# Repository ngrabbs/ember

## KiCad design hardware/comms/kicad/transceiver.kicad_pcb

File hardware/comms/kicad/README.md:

# Comms KiCad project

[Comms home](../README.md) · [Open work](../TODO.md)

Open `transceiver.kicad_pro`. This is the current working all-UHF, single-antenna
project; the former “RX rebuild pending” description is superseded.

| File | Purpose |
|---|---|
| `transceiver.kicad_pro` | Project configuration |
| `transceiver.kicad_sch` and child sheets | Schematic hierarchy |
| `transceiver.kicad_pcb` | Board layout |
| `transceiver.kicad_dru` | Project design rules |
| `lib/`, `sym-lib-table`, `fp-lib-table` | Project symbols, footprints, and library registration |

These files remain tracked.

Follow the [schematic guide](../design/schematic_guide.md),
[shared design rules](../../conventions/kicad_jlcpcb_design_rules.md), and
[RF layout guidance](../design/rf_layout_guidelines.md). Use KiCad/Konnect for design
changes. Prior CLI/native export discrepancies require native connectivity checks
before synchronizing the board.

Fabrication outputs belong in [releases](../releases/README.md).

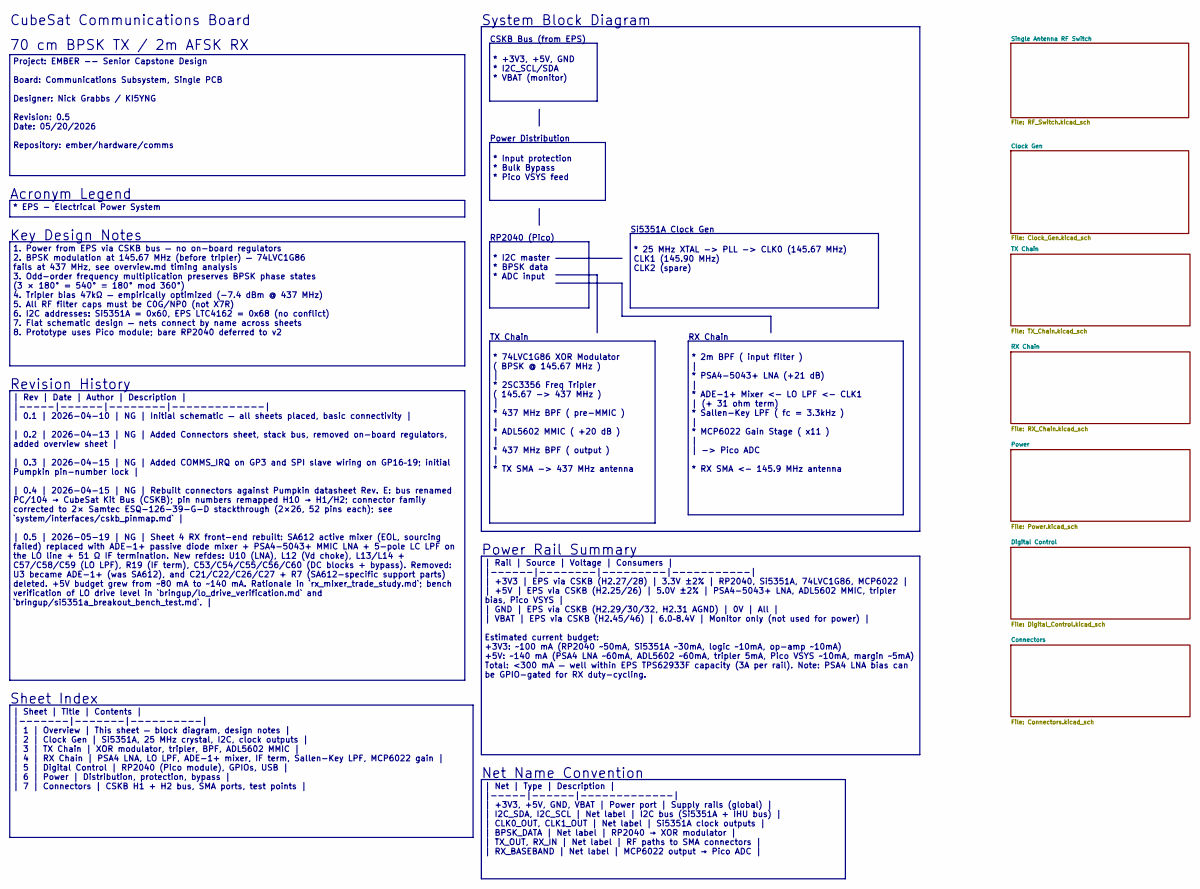
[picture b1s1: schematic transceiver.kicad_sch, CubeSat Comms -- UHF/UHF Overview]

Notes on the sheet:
System Block Diagram
Key Design Notes
Revision History
Si5351A Clock Gen
CSKB Bus (from EPS)
70 cm BPSK TX / 2m AFSK RX
CubeSat Communications Board
Acronym Legend
Power Distribution
Net Name Convention
RX Chain
Power Rail Summary
Sheet Index
RP2040 (Pico)
TX Chain
Project: EMBER -- Senior Capstone Design Board: Communications Subsystem, Single PCB Designer: Nick Grabbs / KI5YNG Revision: 0.5 Date: 05/20/2026 Repository: ember/hardware/comms
| Sheet | Title | Contents | |-------|-------|----------| | 1 | Overview | This sheet — block diagram, design notes | | 2 | Clock Gen | Si5351A, 25 MHz crystal, I2C, clock outputs | | 3 | TX Chain | XOR modulator, tripler, BPF, ADL5602 MMIC | | 4 | RX Chain | PSA4 LNA, LO LPF, ADE-1+ mixer, IF term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
* 74LVC1G86 XOR Modulator ( BPSK @ 145.67 MHz ) | * 2SC3356 Freq Tripler ( 145.67 -> 437 MHz ) | * 437 MHz BPF ( pre-MMIC ) | * ADL5602 MMIC ( +20 dB ) | * 437 MHz BPF ( output ) | * TX SMA -> 437 MHz antenna
* +3V3, +5V, GND * I2C_SCL/SDA * VBAT (monitor)
| Rail | Source | Voltage | Consumers | |------|--------|---------|-----------| | +3V3 | EPS via CSKB (H2.27/28) | 3.3V ±2% | RP2040, Si5351A, 74LVC1G86, MCP6022 | | +5V | EPS via CSKB (H2.25/26) | 5.0V ±2% | PSA4-5043+ LNA, ADL5602 MMIC, tripler bias, Pico VSYS | | GND | EPS via CSKB (H2.29/30/32,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
1. Power from EPS via CSKB bus — no on-board regulators 2. BPSK modulation at 145.67 MHz (before tripler) — 74LVC1G86 fails at 437 MHz, see overview.md timing analysis 3. Odd-order frequency multiplication preserves BPSK phase states (3 × 180° = 540° ≡ 180° mod 360°) 4. Tripler bias 47kΩ — empirica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
* Input protection * Bulk Bypass * Pico VSYS feed
* 25 MHz XTAL -> PLL -> CLK0 (145.67 MHz) CLK1 (145.90 MHz) CLK2 (spare)
| Net | Type | Description | |-----|------|-------------| | +3V3, +5V, GND, VBAT | Power port | Supply rails (global) | | I2C_SDA, I2C_SCL | Net label | I2C bus (Si5351A + IHU bus) | | CLK0_OUT, CLK1_OUT | Net label | Si5351A clock outputs | | BPSK_DATA | Net label | RP2040 → XOR modulator | | TX_O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
* 2m BPF ( input filter ) | * PSA4-5043+ LNA (+21 dB) | * ADE-1+ Mixer <- LO LPF <- CLK1 | (+ 31 ohm term) * Sallen-Key LPF ( fc = 3.3kHz ) | * MCP6022 Gain Stage ( x11 ) | | -> Pico ADC * RX SMA <- 145.9 MHz antenna
| Rev | Date | Author | Description | |-----|------|--------|-------------| | 0.1 | 2026-04-10 | NG | Initial schematic — all sheets placed, basic connectivity | | 0.2 | 2026-04-13 | NG | Added Connectors sheet, stack bus, removed on-board regulators, added overview sheet | | 0.3 | 2026-04-15 | NG 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
* I2C master * BPSK data * ADC input
* EPS - Electrical Power System

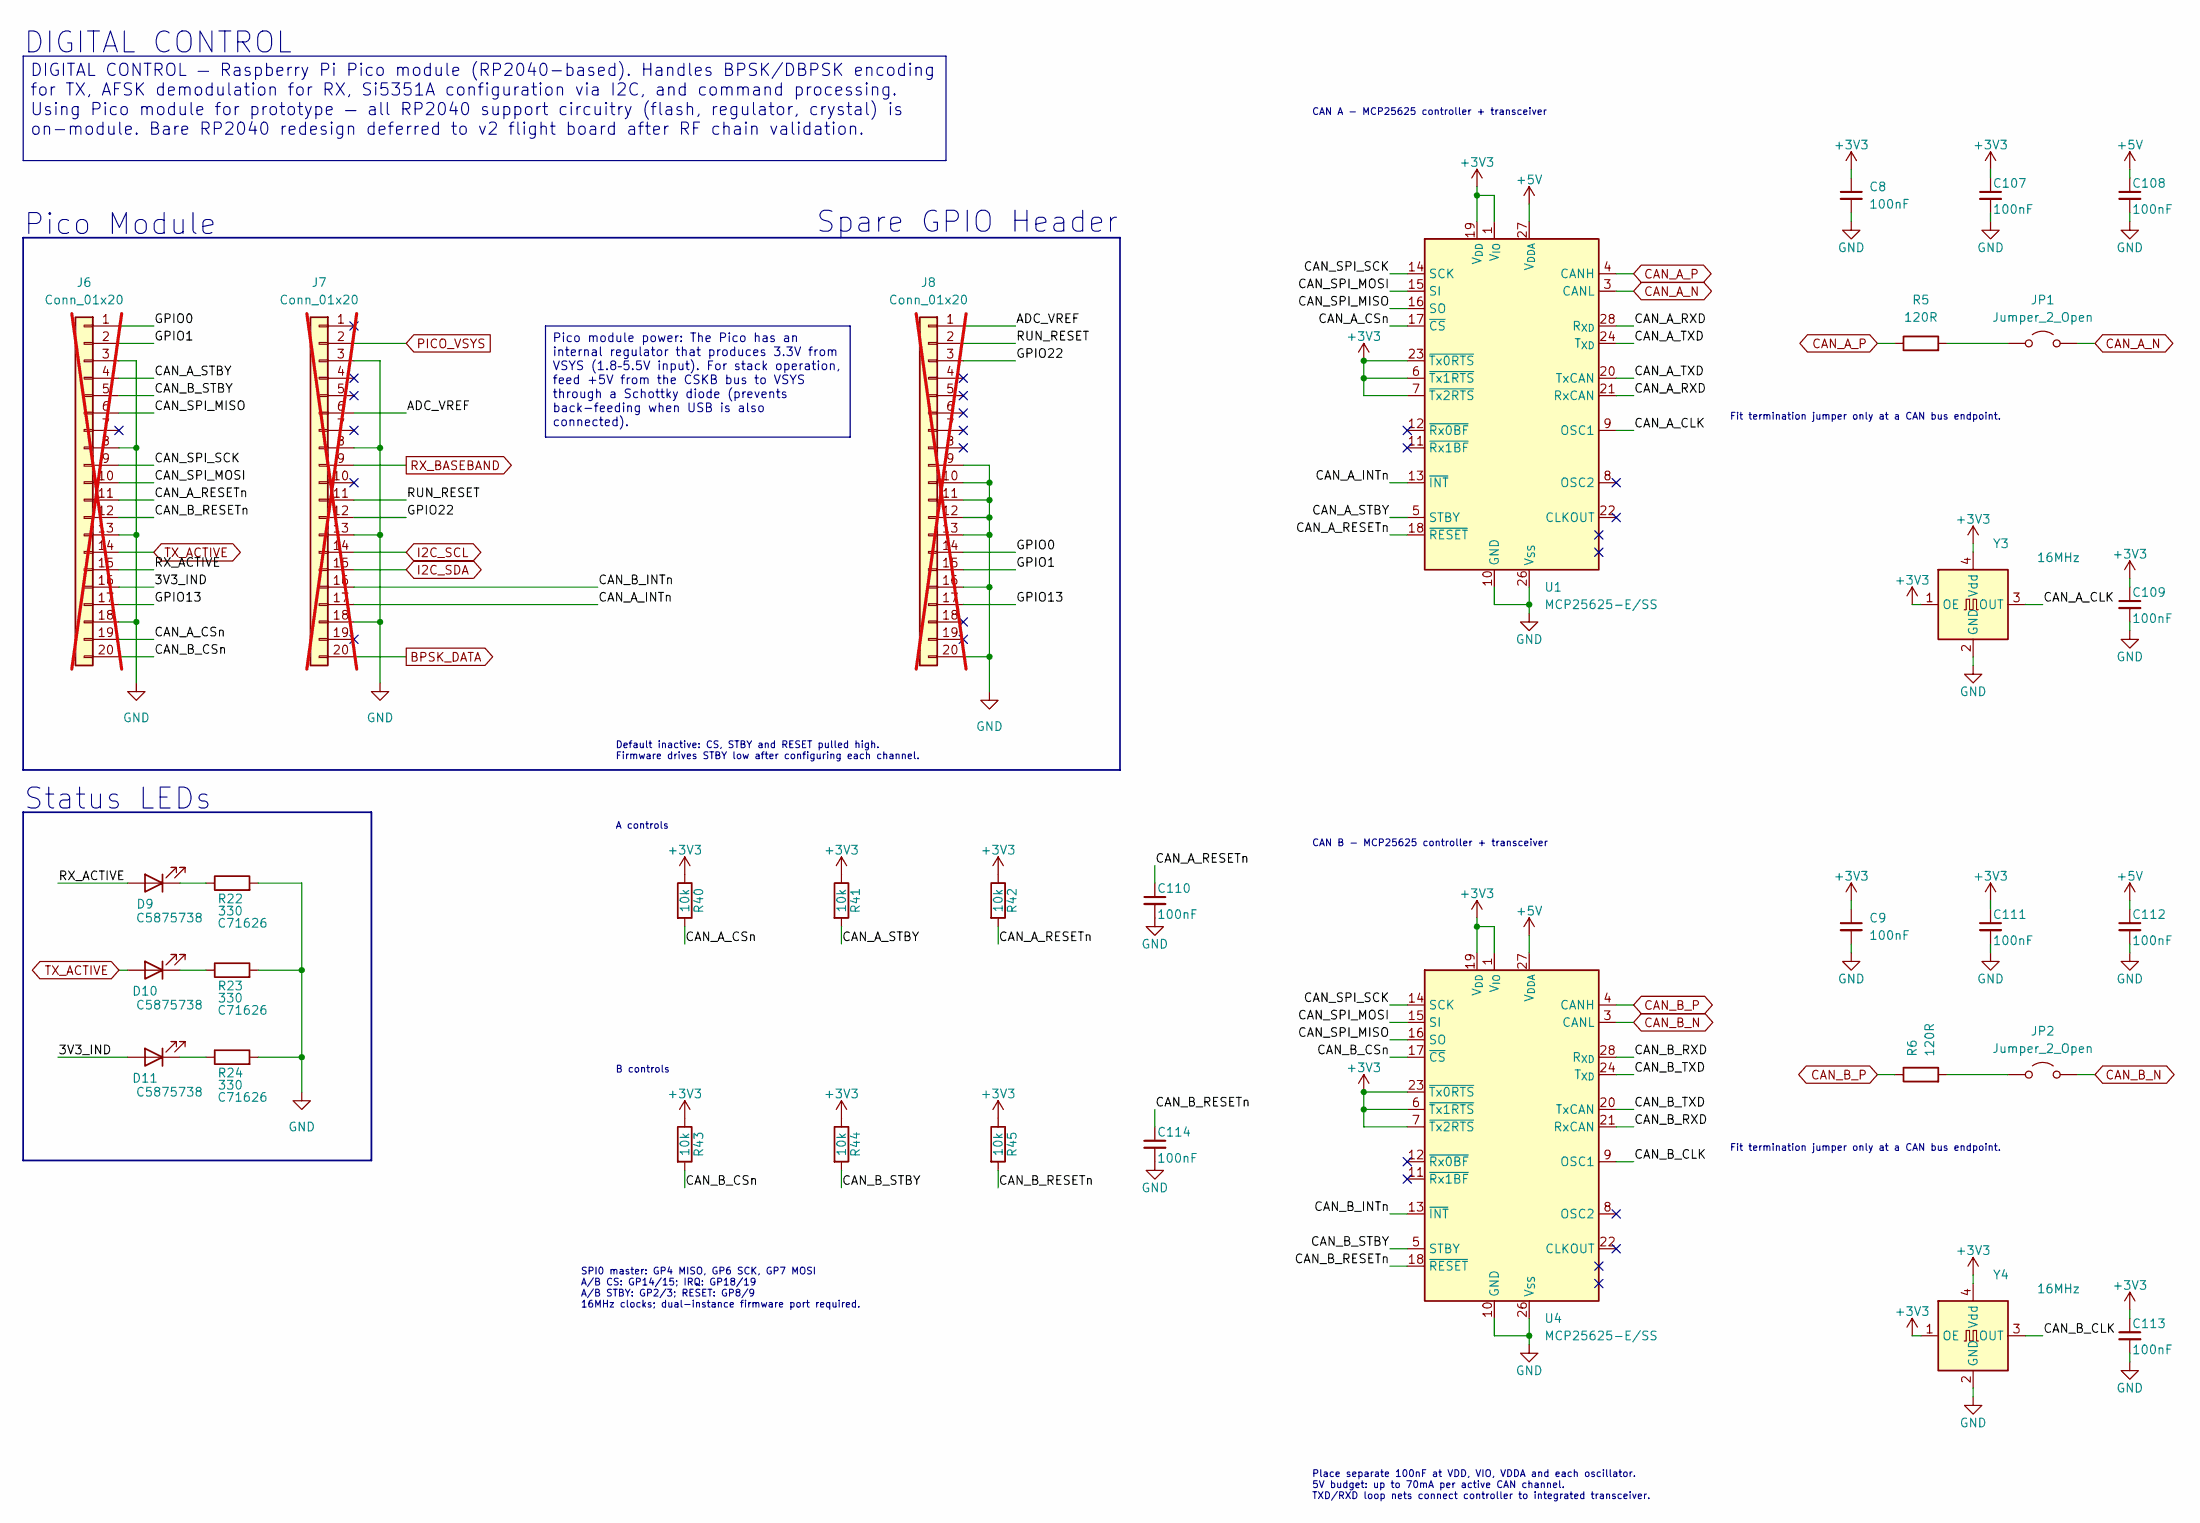
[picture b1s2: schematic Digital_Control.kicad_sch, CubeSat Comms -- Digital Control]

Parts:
C8, C9: 100nF; C_0805_2012Metric; MPN CL21B104KBCNNNC; LCSC Part # C1711
C107, C108, C109, C110, C111, C112, C113, C114: 100nF; C_0603_1608Metric; MPN CC0603KRX7R9BB104; LCSC C14663
D9, D10, D11: LED; LED_0603_1608Metric; LCSC Part # C5875738
J6, J7, J8: Conn_01x20; PinHeader_1x20_P2.54mm_Vertical; MPN 2.54-1*20P; LCSC Part # C50981; not fitted
JP1, JP2: Jumper_2_Open; PinHeader_1x02_P2.54mm_Vertical; MPN 826629-2; LCSC Part # C86471
R5, R6: 120R; R_0805_2012Metric; MPN 0805W8F1200T5E; LCSC Part # C17437
R22, R23, R24: 330; R_0402_1005Metric; LCSC Part # C71626
R40, R41, R42, R43, R44, R45: 10k; R_0603_1608Metric; MPN 0603WAF1002T5E; LCSC C25804
U1, U4: MCP25625-E/SS; SSOP-28_5.3x10.2mm_P0.65mm; MPN MCP25625-E/SS; LCSC C184944
Y3, Y4: 16MHz; Oscillator_SMD_SiT_PQFN-4Pin_7.0x5.0mm; MPN SIT8008AI-82-33E-16.000000Y; LCSC C12710

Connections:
+3V3: C8.1, C9.1, C107.1, C109.1, C111.1, C113.1, R40.1, R41.1, R42.1, R43.1, R44.1, R45.1, U1.1 (V_{IO}), U1.6 (~Tx1RTS), U1.7 (~Tx2RTS), U1.19 (V_{DD}), U1.23 (~Tx0RTS), U4.1 (V_{IO}), U4.6 (~Tx1RTS), U4.7 (~Tx2RTS), U4.19 (V_{DD}), U4.23 (~Tx0RTS), Y3.1 (OE), Y3.4 (Vdd), Y4.1 (OE), Y4.4 (Vdd); also elsewhere on the board
+5V: C108.1, C112.1, U1.27 (V_{DDA}), U4.27 (V_{DDA}); also elsewhere on the board
/Digital Control/3V3_IND: D11.2 (A), J6.16
/Digital Control/ADC_VREF: J7.6, J8.1
/Digital Control/CAN_A_CLK: U1.9 (OSC1), Y3.3 (OUT)
/Digital Control/CAN_A_CSn: J6.19, R40.2, U1.17 (~CS)
/Digital Control/CAN_A_INTn: J7.17, U1.13 (~INT)
/Digital Control/CAN_A_RESETn: C110.1, J6.11, R42.2, U1.18 (~RESET)
/Digital Control/CAN_A_RXD: U1.21 (RxCAN), U1.28 (R_{XD})
/Digital Control/CAN_A_STBY: J6.4, R41.2, U1.5 (STBY)
/Digital Control/CAN_A_TXD: U1.20 (TxCAN), U1.24 (T_{XD})
/Digital Control/CAN_B_CLK: U4.9 (OSC1), Y4.3 (OUT)
/Digital Control/CAN_B_CSn: J6.20, R43.2, U4.17 (~CS)
/Digital Control/CAN_B_INTn: J7.16, U4.13 (~INT)
/Digital Control/CAN_B_RESETn: C114.1, J6.12, R45.2, U4.18 (~RESET)
/Digital Control/CAN_B_RXD: U4.21 (RxCAN), U4.28 (R_{XD})
/Digital Control/CAN_B_STBY: J6.5, R44.2, U4.5 (STBY)
/Digital Control/CAN_B_TXD: U4.20 (TxCAN), U4.24 (T_{XD})
/Digital Control/CAN_SPI_MISO: J6.6, U1.16 (SO), U4.16 (SO)
/Digital Control/CAN_SPI_MOSI: J6.10, U1.15 (SI), U4.15 (SI)
/Digital Control/CAN_SPI_SCK: J6.9, U1.14 (SCK), U4.14 (SCK)
/Digital Control/GPIO0: J6.1, J8.14
/Digital Control/GPIO1: J6.2, J8.15
/Digital Control/GPIO13: J6.17, J8.17
/Digital Control/GPIO22: J7.12, J8.3
/Digital Control/RUN_RESET: J7.11, J8.2
/Digital Control/RX_ACTIVE: D9.2 (A), J6.15
BPSK_DATA: J7.20; also elsewhere on the board
CAN_A_N: JP1.2 (B), U1.3 (CANL); also elsewhere on the board
CAN_A_P: R5.1, U1.4 (CANH); also elsewhere on the board
CAN_B_N: JP2.2 (B), U4.3 (CANL); also elsewhere on the board
CAN_B_P: R6.1, U4.4 (CANH); also elsewhere on the board
GND: C8.2, C9.2, C107.2, C108.2, C109.2, C110.2, C111.2, C112.2, C113.2, C114.2, J6.3, J6.8, J6.13, J6.18, J7.3, J7.8, J7.13, J7.18, J8.9, J8.10, J8.11, J8.12, J8.13, J8.16, J8.20, R22.2, R23.2, R24.2, U1.10 (GND), U1.26 (V_{SS}), U4.10 (GND), U4.26 (V_{SS}), Y3.2 (GND), Y4.2 (GND); also elsewhere on the board
I2C_SCL: J7.14; also elsewhere on the board
I2C_SDA: J7.15; also elsewhere on the board
unnamed: D9.1 (K), R22.1
unnamed: D10.1 (K), R23.1
unnamed: D11.1 (K), R24.1
unnamed: JP1.1 (A), R5.2
unnamed: JP2.1 (A), R6.2
PICO_VSYS: J7.2; also elsewhere on the board
RX_BASEBAND: J7.9; also elsewhere on the board
TX_ACTIVE: D10.2 (A), J6.14; also elsewhere on the board

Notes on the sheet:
Spare GPIO Header
B controls
DIGITAL CONTROL
CAN B - MCP25625 controller + transceiver
CAN A - MCP25625 controller + transceiver
Status LEDs
SPI0 master: GP4 MISO, GP6 SCK, GP7 MOSI A/B CS: GP14/15; IRQ: GP18/19 A/B STBY: GP2/3; RESET: GP8/9 16MHz clocks; dual-instance firmware port required.
Fit termination jumper only at a CAN bus endpoint.
Pico Module
Default inactive: CS, STBY and RESET pulled high. Firmware drives STBY low after configuring each channel.
A controls
Place separate 100nF at VDD, VIO, VDDA and each oscillator. 5V budget: up to 70mA per active CAN channel. TXD/RXD loop nets connect controller to integrated transceiver.
DIGITAL CONTROL — Raspberry Pi Pico module (RP2040-based). Handles BPSK/DBPSK encoding for TX, AFSK demodulation for RX, Si5351A configuration via I2C, and command processing. Using Pico module for prototype — all RP2040 support circuitry (flash, regulator, crystal) is on-module. Bare RP2040 redesi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
Pico module power: The Pico has an internal regulator that produces 3.3V from VSYS (1.8–5.5V input). For stack operation, feed +5V from the CSKB bus to VSYS through a Schottky diode (prevents back-feeding when USB is also connected).

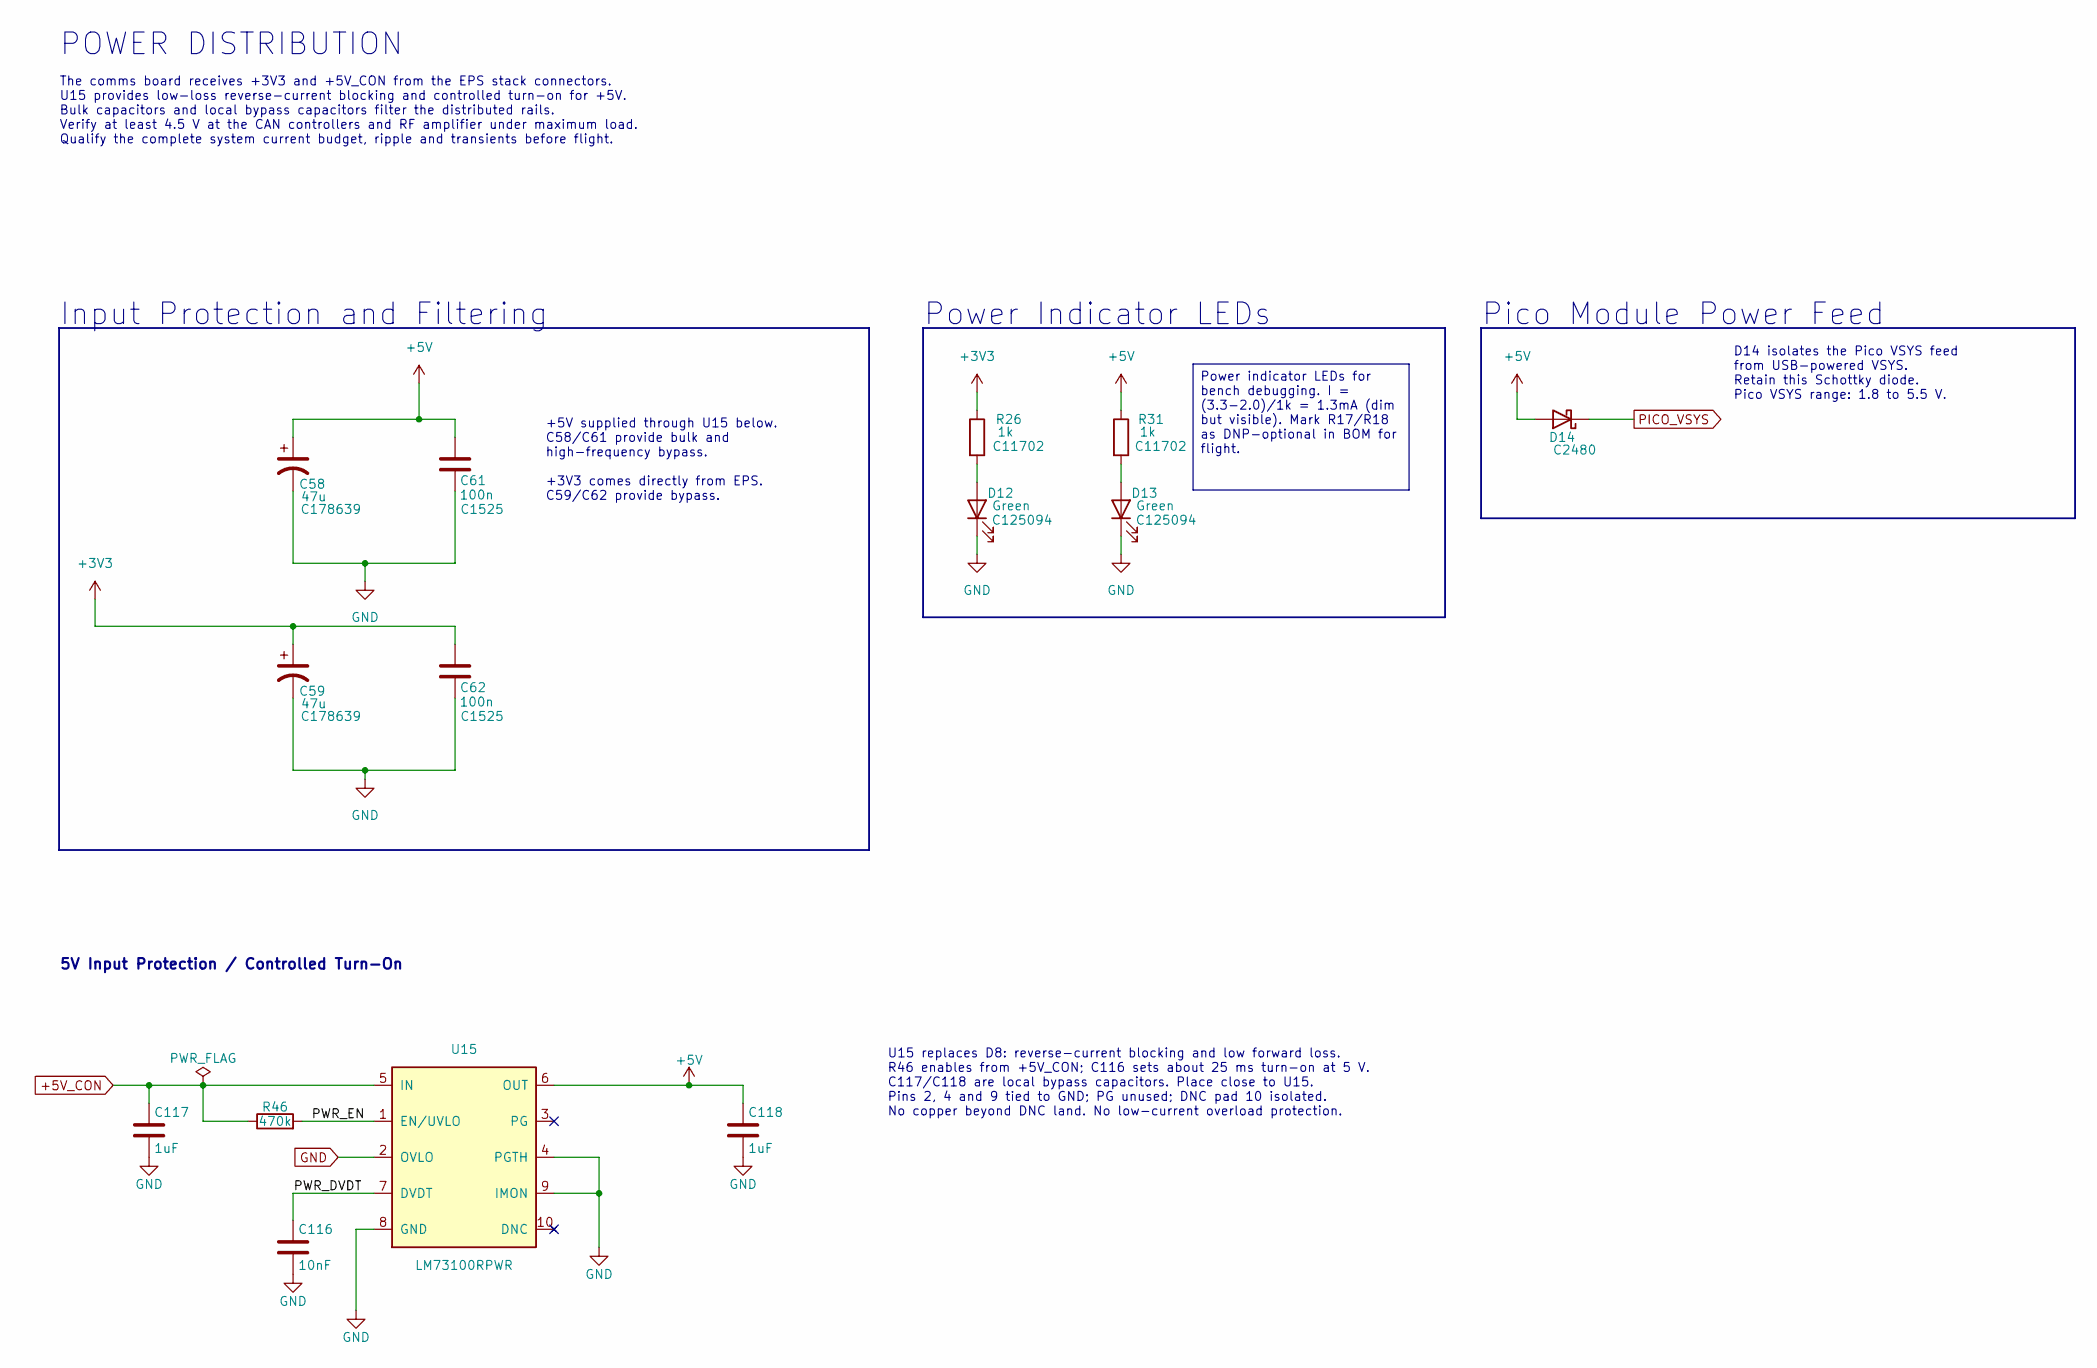
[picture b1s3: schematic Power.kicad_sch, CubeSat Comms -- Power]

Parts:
C58, C59: 47u; CP_Elec_Panasonic_D_6.3x5.8; Voltage 35V; MPN EEHZA1V470P; LCSC Part # C178639
C61, C62: 100n; C_0402_1005Metric; Manufacturer Part # CL05B104KO5NNNC; LCSC Part # C1525
C116: 10nF; C_0603_1608Metric; Tolerance 10%; Voltage Rating 50V; MPN 0603B103K500NT; LCSC Part # C57112
C117, C118: 1uF; C_0603_1608Metric; Tolerance 10%; Voltage Rating 50V; MPN CL10A105KB8NNNC; LCSC Part # C15849
D12, D13: Green; LED_0603_1608Metric; MPN LTST-C190KGKT; LCSC Part # C125094
D14: D_Schottky; D_SMA; LCSC Part # C2480
R26, R31: 1k; R_0402_1005Metric; MPN 0402WGF1001TCE; LCSC Part # C11702
R46: 470k; R_0603_1608Metric; Power Rating 0.1W; Tolerance 1%; MPN 0603WAF4703T5E; LCSC Part # C23178
U15: LM73100RPWR; Texas_RPW0010A_VQFN-HR-10_2x2mm; MPN LM73100RPWR; LCSC Part # C3210761

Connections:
+3V3: C59.1, C62.2, R26.1; also elsewhere on the board
+5V: C58.1, C61.2, C118.1, D14.2 (A), R31.1, U15.6 (OUT); also elsewhere on the board
+5V_CON: C117.1, R46.1, U15.5 (IN); also elsewhere on the board
/Power/PWR_DVDT: C116.1, U15.7 (DVDT)
/Power/PWR_EN: R46.2, U15.1 (EN/UVLO)
GND: C58.2, C59.2, C61.1, C62.1, C116.2, C117.2, C118.2, D12.1 (K), D13.1 (K), U15.2 (OVLO), U15.4 (PGTH), U15.8 (GND), U15.9 (IMON); also elsewhere on the board
unnamed: D12.2 (A), R26.2
unnamed: D13.2 (A), R31.2
PICO_VSYS: D14.1 (K); also elsewhere on the board

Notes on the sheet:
Power Indicator LEDs
+5V supplied through U15 below. C58/C61 provide bulk and high-frequency bypass. +3V3 comes directly from EPS. C59/C62 provide bypass.
5V Input Protection / Controlled Turn-On
Input Protection and Filtering
POWER DISTRIBUTION
Pico Module Power Feed
The comms board receives +3V3 and +5V_CON from the EPS stack connectors. U15 provides low-loss reverse-current blocking and controlled turn-on for +5V. Bulk capacitors and local bypass capacitors filter the distributed rails. Verify at least 4.5 V at the CAN controllers and RF amplifier under maxim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
U15 replaces D8: reverse-current blocking and low forward loss. R46 enables from +5V_CON; C116 sets about 25 ms turn-on at 5 V. C117/C118 are local bypass capacitors. Place close to U15. Pins 2, 4 and 9 tied to GND; PG unused; DNC pad 10 isolated. No copper beyond DNC land. No low-current overload 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
D14 isolates the Pico VSYS feed from USB-powered VSYS. Retain this Schottky diode. Pico VSYS range: 1.8 to 5.5 V.
Power indicator LEDs for bench debugging. I = (3.3-2.0)/1k = 1.3mA (dim but visible). Mark R17/R18 as DNP-optional in BOM for flight.

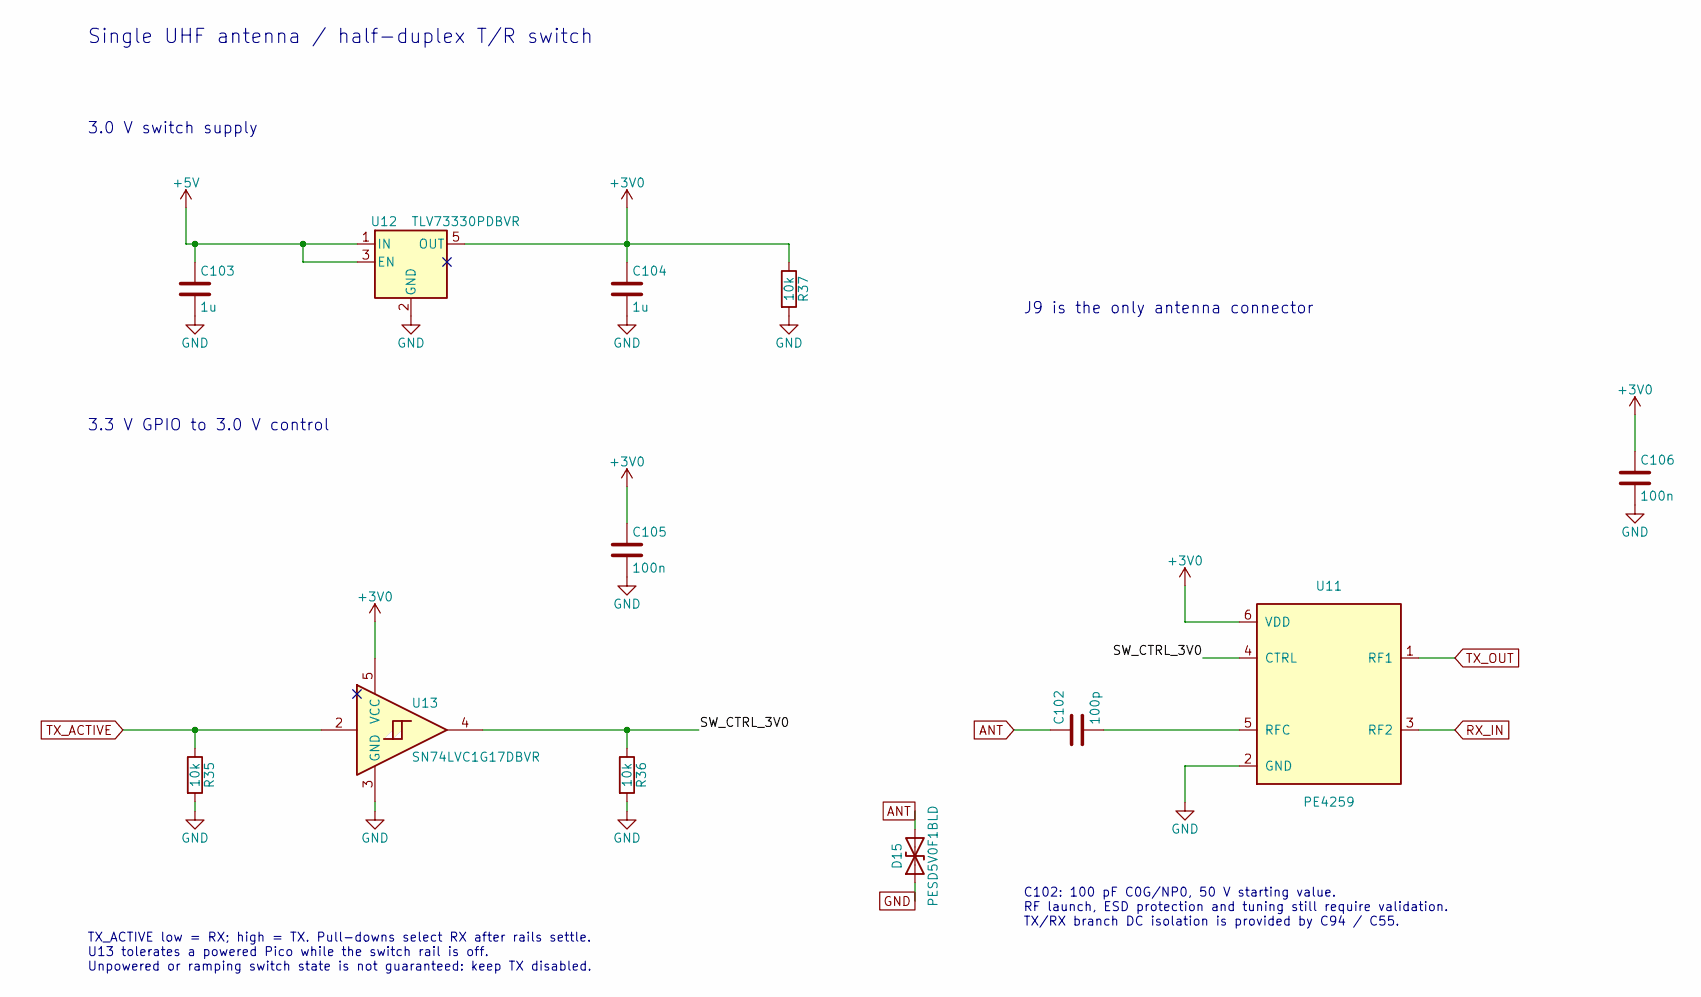
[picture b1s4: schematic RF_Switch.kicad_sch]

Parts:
C102: 100p; C_0402_1005Metric; Tolerance 5%; Voltage 50V; Manufacturer Part # 0402CG101J500NT; LCSC Part # C1546
C103, C104: 1u; C_0603_1608Metric; Voltage 25V; Manufacturer Part # CL10B105KA8NNNC; LCSC Part # C29936
C105, C106: 100n; C_0402_1005Metric; Manufacturer Part # CL05B104KO5NNNC; LCSC Part # C1525
D15: PESD5V0F1BLD; D_SOD-882D; MPN PESD5V0F1BLD,315; LCSC Part # C478204
R35, R36, R37: 10k; R_0402_1005Metric; Manufacturer Part # 0402WGF1002TCE; LCSC Part # C25744
U11: PE4259; SOT-363_SC-70-6; MPN 4259-63; LCSC Part # C470892
U12: TLV73330PDBVR; SOT-23-5; MPN TLV73330PDBVR; LCSC Part # C882826
U13: SN74LVC1G17DBVR; SOT-23-5; MPN SN74LVC1G17DBVR; LCSC Part # C7836

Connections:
+3V0: C104.1, C105.1, C106.1, R37.1, U11.6 (VDD), U12.5 (OUT), U13.5 (VCC)
+5V: C103.1, U12.1 (IN), U12.3 (EN); also elsewhere on the board
/Single Antenna RF Switch/SW_CTRL_3V0: R36.1, U11.4 (CTRL), U13.4
ANT: C102.1, D15.2 (A2); also elsewhere on the board
GND: C103.2, C104.2, C105.2, C106.2, D15.1 (A1), R35.2, R36.2, R37.2, U11.2 (GND), U12.2 (GND), U13.3 (GND); also elsewhere on the board
unnamed: C102.2, U11.5 (RFC)
RX_IN: U11.3 (RF2); also elsewhere on the board
TX_ACTIVE: R35.1, U13.2; also elsewhere on the board
TX_OUT: U11.1 (RF1); also elsewhere on the board

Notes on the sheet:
3.0 V switch supply
C102: 100 pF C0G/NP0, 50 V starting value. RF launch, ESD protection and tuning still require validation. TX/RX branch DC isolation is provided by C94 / C55.
Single UHF antenna / half-duplex T/R switch
3.3 V GPIO to 3.0 V control
J9 is the only antenna connector
TX_ACTIVE low = RX; high = TX. Pull-downs select RX after rails settle. U13 tolerates a powered Pico while the switch rail is off. Unpowered or ramping switch state is not guaranteed: keep TX disabled.

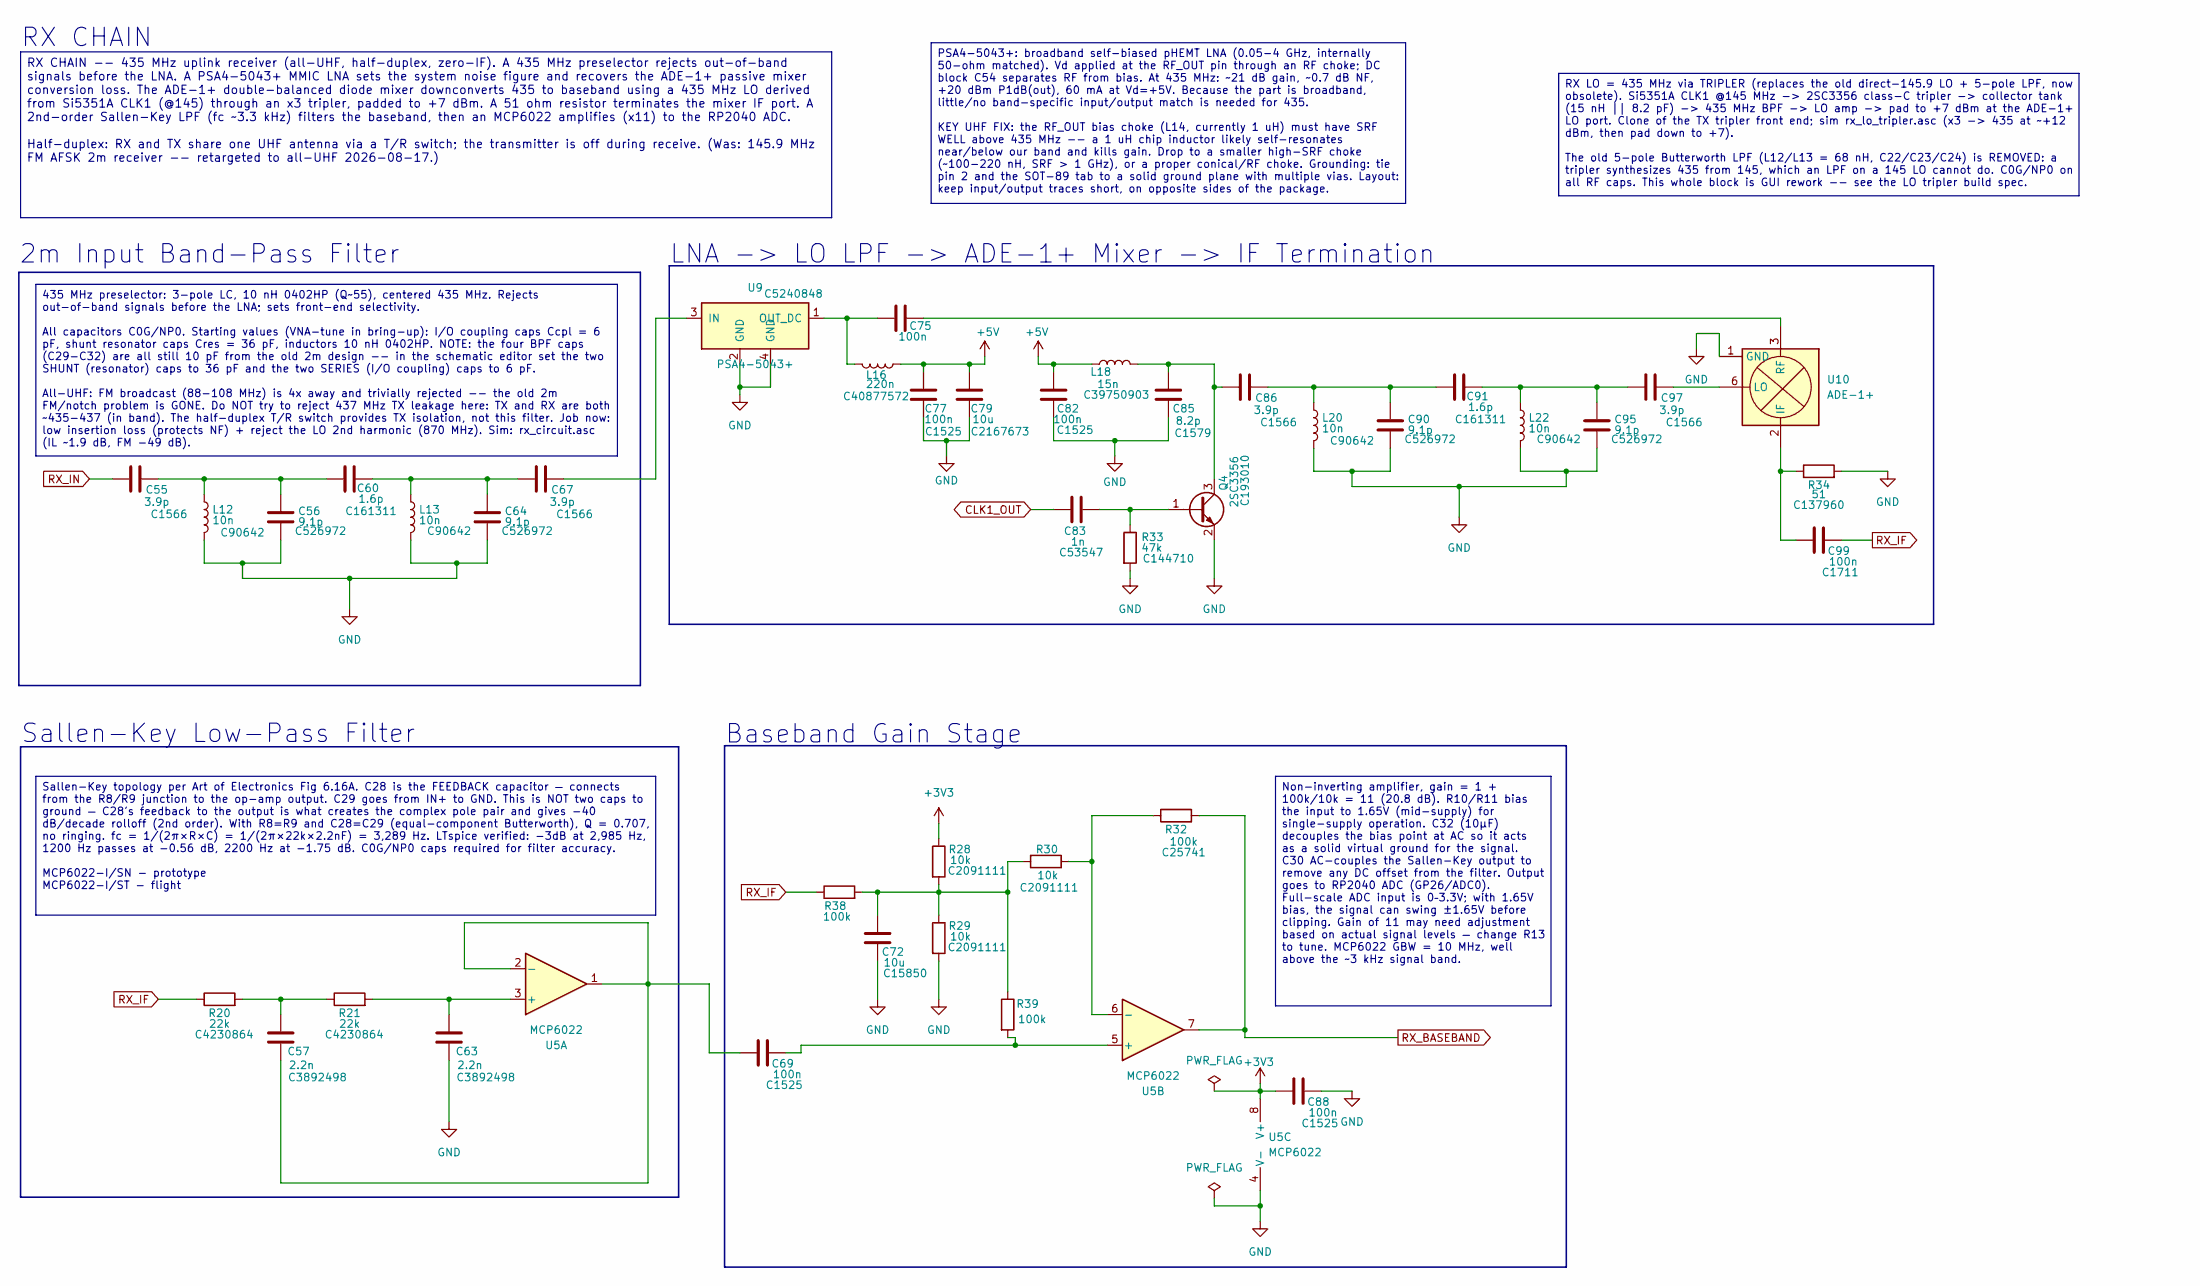
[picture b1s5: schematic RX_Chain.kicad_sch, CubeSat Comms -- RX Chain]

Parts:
C55, C67, C86, C97: 3.9p; C_0402_1005Metric; LCSC Part # C1566
C56, C64, C90, C95: 9.1p; C_0402_1005Metric; LCSC Part # C526972
C57, C63: 2.2n; C_0402_1005Metric; LCSC Part # C3892498
C60, C91: 1.6p; C_0402_1005Metric; LCSC Part # C161311
C69, C75, C77, C82, C88: 100n; C_0402_1005Metric; Manufacturer Part # CL05B104KO5NNNC; LCSC Part # C1525
C72: 10u; C_0805_2012Metric; LCSC Part # C15850
C79: 10u; C_0805_2012Metric; LCSC Part # C2167673
C83: 1n; C_0402_1005Metric; Manufacturer Part # 0402CG102J500NT; LCSC Part # C53547
C85: 8.2p; C_0402_1005Metric; LCSC Part # C1579
C99: 100n; C_0805_2012Metric; Manufacturer Part # CL21B104KBCNNNC; LCSC Part # C1711
L12, L13, L20, L22: 10n; L_0402_1005Metric; MPN LQW15AN10NG00D; LCSC Part # C90642
L16: 220n; L_Coilcraft_0805HP; MPN 0805HP-221XGRC; LCSC Part # C40877572
L18: 15n; L_0402_1005Metric; LCSC Part # C39750903
Q4: 2SC3356; SOT-23; Manufacturer Part # 2SC3356; LCSC Part # C193010
R20, R21: 22k; R_0402_1005Metric; LCSC Part # C4230864
R28, R29, R30: 10k; R_0402_1005Metric; LCSC Part # C2091111
R32, R38, R39: 100k; R_0402_1005Metric; LCSC Part # C25741
R33: 47k; R_0402_1005Metric; LCSC Part # C144710
R34: 51; R_0402_1005Metric; LCSC Part # C137960
U5: MCP6022; SOIC-8_3.9x4.9mm_P1.27mm; MPN MCP6022-I/SN; LCSC Part # C57639
U9: PSA4-5043+; PSA4-5043_MMM1362; MPN PSA4-5043+; LCSC Part # C5240848
U10: ADE-1+; Mini-Circuits_CD542_LandPatternPL-052; MPN ADE-1+; LCSC Part # C2942210

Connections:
+3V3: C88.2, R28.1, U5.8 (V+); also elsewhere on the board
+5V: C77.2, C79.2, C82.2, L16.1, L18.1; also elsewhere on the board
CLK1_OUT: C83.2; also elsewhere on the board
GND: C56.2, C63.2, C64.2, C72.1, C77.1, C79.1, C82.1, C85.2, C88.1, C90.2, C95.2, L12.2, L13.2, L20.2, L22.2, Q4.2 (E), R29.2, R33.2, R34.2, U5.4 (V-), U9.2 (GND), U9.4 (GND), U10.1 (GND), U10.4 (GND), U10.5 (GND); also elsewhere on the board
unnamed: C55.2, C56.1, C60.1, L12.1
unnamed: C57.1, R20.2, R21.1
unnamed: C60.2, C64.1, C67.1, L13.1
unnamed: C86.2, C90.1, C91.1, L20.1
unnamed: C91.2, C95.1, C97.1, L22.1
unnamed: C83.1, Q4.1 (B), R33.1
unnamed: C85.1, C86.1, L18.2, Q4.3 (C)
unnamed: C63.1, R21.2, U5.3 (+)
unnamed: C57.2, C69.2, U5.1, U5.2 (-)
unnamed: R30.1, R32.1, U5.6 (-)
unnamed: C67.2, U9.3 (IN)
unnamed: C75.1, L16.2, U9.1 (OUT_DC)
unnamed: C99.2, R34.1, U10.2 (IF)
unnamed: C97.2, U10.6 (LO)
unnamed: C75.2, U10.3 (RF)
RX_BASEBAND: R32.2, U5.7; also elsewhere on the board
RX_IF: C99.1, R20.1, R38.1; also elsewhere on the board
RX_IN: C55.1; also elsewhere on the board

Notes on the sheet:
Baseband Gain Stage
Sallen-Key Low-Pass Filter
LNA -> LO LPF -> ADE-1+ Mixer -> IF Termination
RX CHAIN
2m Input Band-Pass Filter
Non-inverting amplifier, gain = 1 + 100k/10k = 11 (20.8 dB). R10/R11 bias the input to 1.65V (mid-supply) for single-supply operation. C32 (10µF) decouples the bias point at AC so it acts as a solid virtual ground for the signal. C30 AC-couples the Sallen-Key output to remove any DC offset from the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
Sallen-Key topology per Art of Electronics Fig 6.16A. C28 is the FEEDBACK capacitor — connects from the R8/R9 junction to the op-amp output. C29 goes from IN+ to GND. This is NOT two caps to ground — C28's feedback to the output is what creates the complex pole pair and gives -40 dB/decade rolloff 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
435 MHz preselector: 3-pole LC, 10 nH 0402HP (Q~55), centered 435 MHz. Rejects out-of-band signals before the LNA; sets front-end selectivity. All capacitors C0G/NP0. Starting values (VNA-tune in bring-up): I/O coupling caps Ccpl = 6 pF, shunt resonator caps Cres = 36 pF, inductors 10 nH 0402HP. NO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
RX LO = 435 MHz via TRIPLER (replaces the old direct-145.9 LO + 5-pole LPF, now obsolete). Si5351A CLK1 @145 MHz -> 2SC3356 class-C tripler -> collector tank (15 nH || 8.2 pF) -> 435 MHz BPF -> LO amp -> pad to +7 dBm at the ADE-1+ LO port. Clone of the TX tripler front end; sim rx_lo_tripler.asc (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
RX CHAIN -- 435 MHz uplink receiver (all-UHF, half-duplex, zero-IF). A 435 MHz preselector rejects out-of-band signals before the LNA. A PSA4-5043+ MMIC LNA sets the system noise figure and recovers the ADE-1+ passive mixer conversion loss. The ADE-1+ double-balanced diode mixer downconverts 435 to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
PSA4-5043+: broadband self-biased pHEMT LNA (0.05-4 GHz, internally 50-ohm matched). Vd applied at the RF_OUT pin through an RF choke; DC block C54 separates RF from bias. At 435 MHz: ~21 dB gain, ~0.7 dB NF, +20 dBm P1dB(out), 60 mA at Vd=+5V. Because the part is broadband, little/no band-specific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

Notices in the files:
parts and their libraries:
COPYRIGHT: Copyright (C) 2026 Ultra Librarian. All rights reserved.
COPYRIGHT: Copyright (C) 2025 Ultra Librarian. All rights reserved.
